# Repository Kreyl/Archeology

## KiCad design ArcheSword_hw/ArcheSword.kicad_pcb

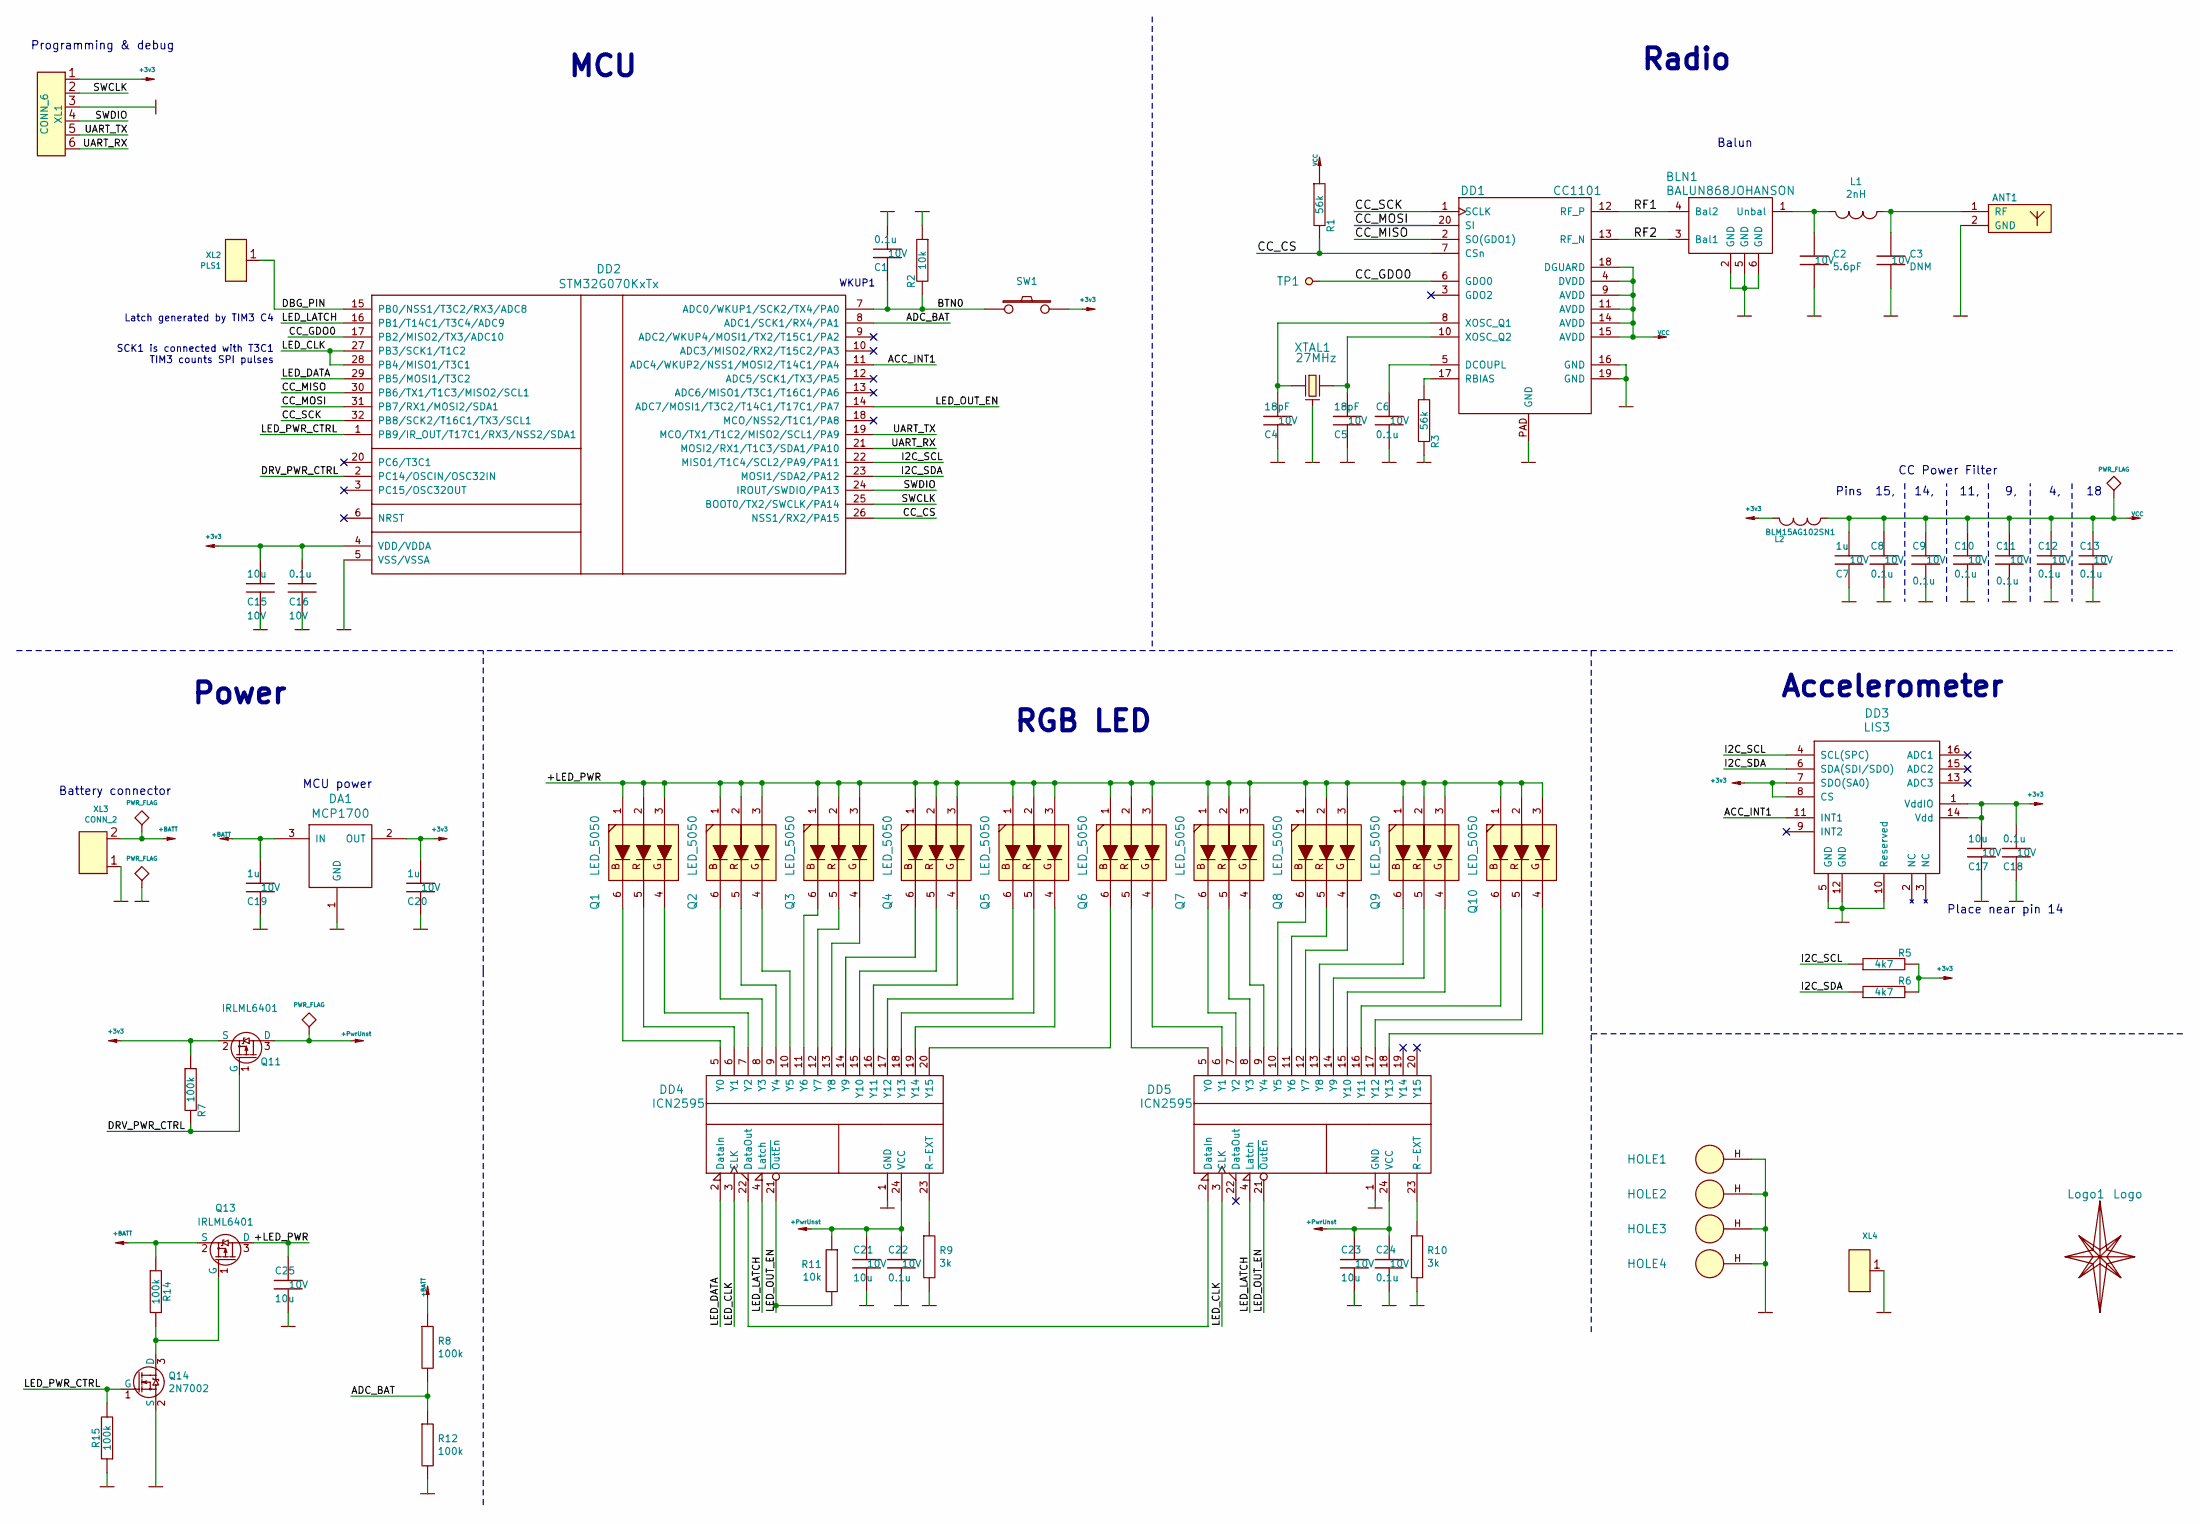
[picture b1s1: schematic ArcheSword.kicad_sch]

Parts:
ANT1: ANT_GENERAL; Locket5
BLN1: BALUN868JOHANSON; BALUN_JOHANSON868
C1, C6, C8, C9, C10, C11, C12, C13, C18, C22, C24: 0.1u; CAP_0603_Silks; Tolerance 20%; Voltage 10V
C2: 5.6pF; CAP_0402; Tolerance 20%; Voltage 10V
C3: DNM; CAP_0402; Tolerance 20%; Voltage 10V
C4, C5: 18pF; CAP_0603_Silks; Tolerance 20%; Voltage 10V
C7, C19, C20: 1u; CAP_0603_Silks; Tolerance 20%; Voltage 10V
C15: 10u; CAP_0603_Silks; Voltage 10V; Tolerance 20%
C16: 0.1u; CAP_0603_Silks; Voltage 10V; Tolerance 20%
C17, C21, C23, C25: 10u; CAP_0603_Silks; Tolerance 20%; Voltage 10V
DA1: MCP1700; SOT23-3A
DD1: CC1101; QFN20
DD2: STM32G070KxTx; TQFP-32_7x7_Pitch0.8mm
DD3: LIS3; LGA16_3X3_5_3
DD4, DD5: ICN2595; TSSOP24_150_0635
HOLE1, HOLE2, HOLE3, HOLE4: HOLE_METALLED; Hole3_5_out6mm
L1: 2nH; IND_0402; Tolerance 20%
L2: BLM15AG102SN1; IND_0402; Tolerance 20%
Logo1: Logo; Ostranna_16d9_13d5
Q1, Q2, Q3, Q4, Q5, Q6, Q7, Q8, Q9, Q10: LED_5050
Q11, Q13: IRLML6401; SOT23-3
Q14: 2N7002; SOT23-3
R1, R3: 56k; RES_0603; Tolerance 1%
R2, R11: 10k; RES_0603; Tolerance 1%
R5, R6: 4k7; RES_0603; Tolerance 1%
R7, R8, R12: 100k; RES_0603; Tolerance 1%
R9, R10: 3k; RES_0603; Tolerance 1%
R14, R15: 100k; RES_0603
SW1: BUTTON; BTN_4x4_SMD
TP1: TESTPOINT; TESTPOINT_1MM
XL1: CONN_6; PLS-6_LOCK
XL2: PLS1; PLS-1Rnd
XL3: CONN_2; SLD_2_2D5
XL4: CONN_1; PLS-1Square
XTAL1: 27MHz; 03225C4

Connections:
+3v3: C15.1, C16.1, C17.1, C18.1, C20.1, DA1.2 (OUT), DD2.4 (VDD/VDDA), DD3.1 (VddIO), DD3.7 (SDO(SA0)), DD3.8 (CS), DD3.14 (Vdd), L2.2, Q11.2 (S), R5.2, R6.2, R7.1, SW1.2, XL1.1
+BATT: C19.1, DA1.3 (IN), Q13.2 (S), R8.1, R14.1, XL3.2 (PM)
+PwrUnst: C21.2, C22.2, C23.2, C24.2, DD4.24 (VCC), DD5.24 (VCC), Q11.3 (D), R11.1
/+LED_PWR: C25.2, Q1.1, Q1.2, Q1.3, Q2.1, Q2.2, Q2.3, Q3.1, Q3.2, Q3.3, Q4.1, Q4.2, Q4.3, Q5.1, Q5.2, Q5.3, Q6.1, Q6.2, Q6.3, Q7.1, Q7.2, Q7.3, Q8.1, Q8.2, Q8.3, Q9.1, Q9.2, Q9.3, Q10.1, Q10.2, Q10.3, Q13.3 (D)
/ACC_INT1: DD2.11 (ADC4/WKUP2/NSS1/MOSI2/T14C1/PA4), DD3.11 (INT1)
/ADC_BAT: DD2.8 (ADC1/SCK1/RX4/PA1), R8.2, R12.1
/BTN0: C1.2, DD2.7 (ADC0/WKUP1/SCK2/TX4/PA0), R2.2, SW1.1
/CC_CS: DD1.7 (CSn), DD2.26 (NSS1/RX2/PA15), R1.2
/CC_GDO0: DD1.6 (GDO0), DD2.17 (PB2/MISO2/TX3/ADC10), TP1.1
/CC_MISO: DD1.2 (SO(GDO1)), DD2.30 (PB6/TX1/T1C3/MISO2/SCL1)
/CC_MOSI: DD1.20 (SI), DD2.31 (PB7/RX1/MOSI2/SDA1)
/CC_SCK: DD1.1 (SCLK), DD2.32 (PB8/SCK2/T16C1/TX3/SCL1)
/DBG_PIN: DD2.15 (PB0/NSS1/T3C2/RX3/ADC8), XL2.1
/DRV_PWR_CTRL: DD2.2 (PC14/OSCIN/OSC32IN), Q11.1 (G), R7.2
/I2C_SCL: DD2.22 (MISO1/T1C4/SCL2/PA9/PA11), DD3.4 (SCL(SPC)), R5.1
/I2C_SDA: DD2.23 (MOSI1/SDA2/PA12), DD3.6 (SDA(SDI/SDO)), R6.1
/LED_CLK: DD2.27 (PB3/SCK1/T1C2), DD2.28 (PB4/MISO1/T3C1), DD4.3 (CLK), DD5.3 (CLK)
/LED_DATA: DD2.29 (PB5/MOSI1/T3C2), DD4.2 (DataIn)
/LED_LATCH: DD2.16 (PB1/T14C1/T3C4/ADC9), DD4.4 (Latch), DD5.4 (Latch)
/LED_OUT_EN: DD2.14 (ADC7/MOSI1/T3C2/T14C1/T17C1/PA7), DD4.21 (~OutEn), DD5.21 (~OutEn), R11.2
/LED_PWR_CTRL: DD2.1 (PB9/IR_OUT/T17C1/RX3/NSS2/SDA1), Q14.1 (G), R15.2
/RF1: BLN1.4 (Bal2), DD1.12 (RF_P)
/RF2: BLN1.3 (Bal1), DD1.13 (RF_N)
/SWCLK: DD2.25 (BOOT0/TX2/SWCLK/PA14), XL1.2
/SWDIO: DD2.24 (IROUT/SWDIO/PA13), XL1.4
/UART_RX: DD2.21 (MOSI2/RX1/T1C3/SDA1/PA10), XL1.6
/UART_TX: DD2.19 (MCO/TX1/T1C2/MISO2/SCL1/PA9), XL1.5
GND: ANT1.2 (GND), BLN1.2 (GND), BLN1.5 (GND), BLN1.6 (GND), C1.1, C2.2, C3.2, C4.2, C5.2, C6.1, C7.2, C8.2, C9.2, C10.2, C11.2, C12.2, C13.2, C15.2, C16.2, C17.2, C18.2, C19.2, C20.2, C21.1, C22.1, C23.1, C24.1, C25.1, DA1.1 (GND), DD1.16 (GND), DD1.19 (GND), DD1.PAD (GND), DD2.5 (VSS/VSSA), DD3.5 (GND), DD3.10 (Reserved), DD3.12 (GND), DD4.1 (GND), DD5.1 (GND), HOLE1.H, HOLE2.H, HOLE3.H, HOLE4.H, Q14.2 (S), R2.1, R3.2, R9.2, R10.2, R12.2, R15.1, XL1.3, XL3.1, XL4.1, XTAL1.H
unnamed: ANT1.1 (RF), C3.1, L1.2
unnamed: BLN1.1 (Unbal), C2.1, L1.1
unnamed: C4.1, DD1.8 (XOSC_Q1), XTAL1.1
unnamed: C5.1, DD1.10 (XOSC_Q2), XTAL1.2
unnamed: C6.2, DD1.5 (DCOUPL)
unnamed: DD1.17 (RBIAS), R3.1
unnamed: DD4.5 (Y0), Q1.6
unnamed: DD4.6 (Y1), Q1.5 (G)
unnamed: DD4.7 (Y2), Q1.4 (B)
unnamed: DD4.8 (Y3), Q2.6
unnamed: DD4.9 (Y4), Q2.5 (G)
unnamed: DD4.10 (Y5), Q2.4 (B)
unnamed: DD4.11 (Y6), Q3.6
unnamed: DD4.12 (Y7), Q3.5 (G)
unnamed: DD4.13 (Y8), Q3.4 (B)
unnamed: DD4.14 (Y9), Q4.6
unnamed: DD4.15 (Y10), Q4.5 (G)
unnamed: DD4.16 (Y11), Q4.4 (B)
unnamed: DD4.17 (Y12), Q5.6
unnamed: DD4.18 (Y13), Q5.5 (G)
unnamed: DD4.19 (Y14), Q5.4 (B)
unnamed: DD4.20 (Y15), Q6.6
unnamed: DD4.22 (DataOut), DD5.2 (DataIn)
unnamed: DD4.23 (R-EXT), R9.1
unnamed: DD5.5 (Y0), Q6.5 (G)
unnamed: DD5.6 (Y1), Q6.4 (B)
unnamed: DD5.7 (Y2), Q7.6
unnamed: DD5.8 (Y3), Q7.5 (G)
unnamed: DD5.9 (Y4), Q7.4 (B)
unnamed: DD5.10 (Y5), Q8.6
unnamed: DD5.11 (Y6), Q8.5 (G)
unnamed: DD5.12 (Y7), Q8.4 (B)
unnamed: DD5.13 (Y8), Q9.6
unnamed: DD5.14 (Y9), Q9.5 (G)
unnamed: DD5.15 (Y10), Q9.4 (B)
unnamed: DD5.16 (Y11), Q10.6
unnamed: DD5.17 (Y12), Q10.5 (G)
unnamed: DD5.18 (Y13), Q10.4 (B)
unnamed: DD5.23 (R-EXT), R10.1
unnamed: Q13.1 (G), Q14.3 (D), R14.2
VCC: C7.1, C8.1, C9.1, C10.1, C11.1, C12.1, C13.1, DD1.4 (DVDD), DD1.9 (AVDD), DD1.11 (AVDD), DD1.14 (AVDD), DD1.15 (AVDD), DD1.18 (DGUARD), L2.1, R1.1

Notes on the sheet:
Programming & debug
Battery connector
Power
Latch generated by TIM3 C4
SCK1 is connected with T3C1 TIM3 counts SPI pulses
MCU power
MCU
WKUP1
RGB LED
Radio
Balun
Accelerometer
Pins 15, 14, 11, 9, 4, 18
CC Power Filter
Place near pin 14

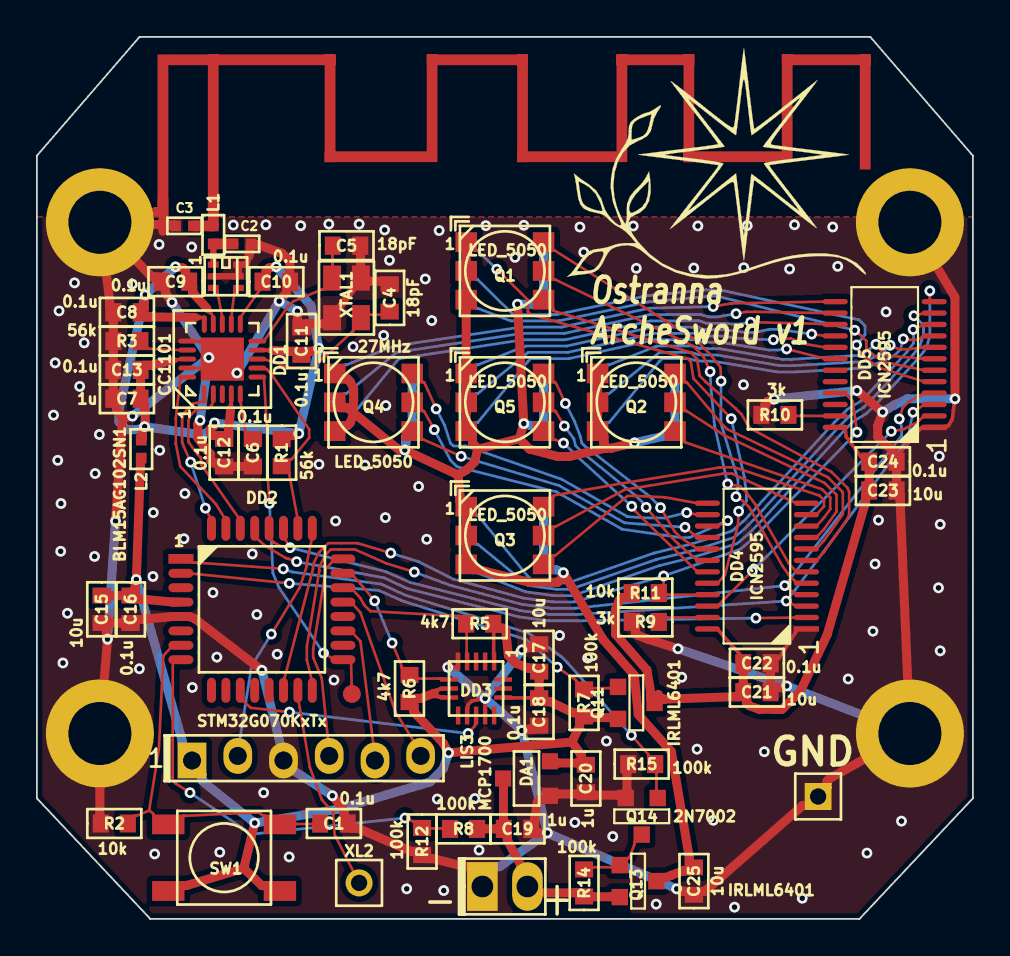
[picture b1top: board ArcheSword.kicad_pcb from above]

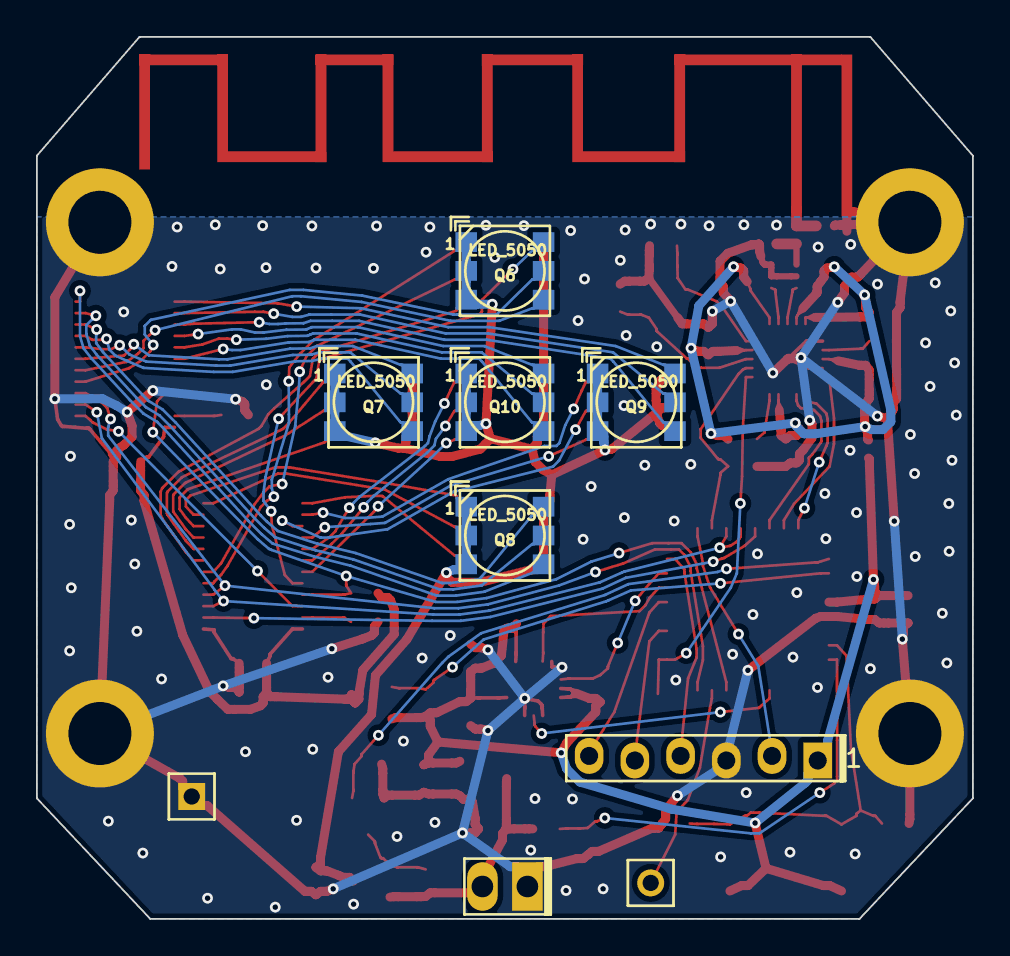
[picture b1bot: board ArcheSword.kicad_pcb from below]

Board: 2 copper layers, 52.0 x 49.0 mm, 72 parts (5 on the bottom side), 69 nets.

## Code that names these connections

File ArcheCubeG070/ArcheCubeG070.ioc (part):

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Mcu.Name=STM32G070KBTx
Mcu.Package=LQFP32
Mcu.UserName=STM32G070KBTx
PA0.Mode=SYS_WakeUp0
PA0.Signal=SYS_WKUP1
PA1.Mode=IN1
PA1.Signal=ADC1_IN1
PA10.Mode=Asynchronous
PA10.Signal=USART1_RX
PA11\ [PA9].Mode=I2C
PA11\ [PA9].Signal=I2C2_SCL
PA12\ [PA10].Mode=I2C
PA12\ [PA10].Signal=I2C2_SDA
PA13.Mode=Serial_Wire
PA13.Signal=SYS_SWDIO
PA14-BOOT0.Mode=Serial_Wire
PA14-BOOT0.Signal=SYS_SWCLK
PA15.Signal=GPIO_Output
PA2.Signal=GPIO_Output
PA4.Mode=SYS_WakeUp1
PA4.Signal=SYS_WKUP2
PA7.Signal=S_TIM3_CH2
PA9.Mode=Asynchronous
PA9.Signal=USART1_TX
PB0.Signal=GPIO_Output
PB1.Signal=S_TIM3_CH4
PB2.Signal=GPIO_Input
PB3.Mode=TX_Only_Simplex_Unidirect_Master
PB3.Signal=SPI1_SCK
PB4.Signal=S_TIM3_CH1
PB5.Mode=TX_Only_Simplex_Unidirect_Master
PB5.Signal=SPI1_MOSI
PB6.Mode=Full_Duplex_Master
PB6.Signal=SPI2_MISO
PB7.Mode=Full_Duplex_Master
PB7.Signal=SPI2_MOSI
PB8.Mode=Full_Duplex_Master
PB8.Signal=SPI2_SCK
PB9.Signal=GPIO_Output
PC14-OSC32_IN\ (PC14).Signal=GPIO_Output
RCC.HSE_VALUE=8000000
RCC.SYSCLKFreq_VALUE=64000000
RCC.SYSCLKSource=RCC_SYSCLKSOURCE_PLLCLK
board=custom

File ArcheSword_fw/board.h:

#pragma once

// ==== General ====
#define BOARD_NAME          "ArcheoSword"
#define APP_NAME            "ArcheoSword"

#define LSE_FREQ_HZ     32768   // Left it here even if not used

// ST driver system settings
#define STM32_ST_IRQ_PRIORITY   2
#define STM32_ST_USE_TIMER      15

#ifndef TRUE
#define TRUE            1
#endif

#if 1 // ========================== GPIO =======================================
// UART
#define UART_GPIO       GPIOA
#define UART_TX_PIN     9
#define UART_RX_PIN     10

// I2C
#define SCL2_GPIO       GPIOA
#define SCL2_PIN        11
#define SDA2_GPIO       GPIOA
#define SDA2_PIN        12
#define I2C2_AF         AF6

// Counts
#define LED_CNT         10UL // Max
#define LED_CHNL_CNT    (LED_CNT * 3UL)
#define LED_BYTE_CNT    4UL // 2 ICs, 32 bits
#define LED_WORD_CNT    2UL // DISP_BYTE_CNT / 2
#define LED_IC_CNT      2UL

// Debug pin
#define DBG_PIN         GPIOB, 0
#define DBG_HI()        PinSetHi(DBG_PIN)
#define DBG_LO()        PinSetLo(DBG_PIN)
#define DBG_TOGGLE()    PinToggle(DBG_PIN)

// LEDs
#define TIMESLOT_TOP    255UL
#define OUT_EN_PIN      GPIOA, 7, omPushPull, pudNone, AF1
#define LATCH_TMR       TIM3
#define LEDS_SPI        SPI1
#define LATCH_TMR_IN    GPIOB, 4, omPushPull, pudPullDown, AF1
#define LATCH_PIN       GPIOB, 1, omPushPull, pudNone, AF1
#define LED_DATA        GPIOB, 5, omPushPull, pudNone, AF0
#define LED_CLK         GPIOB, 3, omPushPull, pudNone, AF0
#define LED_PWR_CTRL    GPIOB, 9
#define DRV_PWR_CTRL    GPIOC, 14

// Radio: SPI, PGpio, Sck, Miso, Mosi, Cs, Gdo0
#define CC_Setup0       SPI2, GPIOB, 8,6,7, GPIOA,15, GPIOB,2

// Acc
#define ACG_IRQ_PIN     GPIOA, 4

#define ADC_BAT         GPIOA, 1

// Button
#define BTN_PIN         GPIOA, 0
#endif // GPIO

#if 1 // =========================== I2C =======================================
#define I2C1_ENABLED        FALSE
#define I2C2_ENABLED        FALSE
#define I2C_BAUDRATE_HZ     400000
#define I2C_USE_DMA         FALSE
#endif

#if 1 // =========================== ADC =======================================
#define ADC_ENABLED     FALSE
#define ADC_CHNL_CNT    2 // Tsns and VRef

#endif

#if 1 // =========================== Timers ====================================
#define LEDS_TIM        TIM3
#define LEDS_TIM_IRQ_VECTOR TIM3_IRQHandler

#define TIME_TIMER      TIM7
#define ADC_TIMER       TIM6

#endif


#if 1 // =========================== DMA =======================================
// ==== Uart ====
#define UART_DMA_TX_CHNL    7
#define UART_DMA_TX_REQID   51 // p223 of refman
#define UART_DMA_RX_CHNL    6
#define UART_DMA_RX_REQID   50 // p223 of refman

#define UART_DMA_TX_MODE (  DMA_PRIORITY_LOW | \
                            DMA_MSIZE_8_BIT | \
                            DMA_PSIZE_8_BIT | \
                            DMA_MEM_INC |       /* Memory pointer increase */ \
                            DMA_DIR_MEM2PER |    /* Direction is memory to peripheral */ \
                            DMA_TCIE         /* Enable Transmission Complete IRQ */)

#define UART_DMA_RX_MODE (  DMA_PRIORITY_MEDIUM | \
                            DMA_MSIZE_8_BIT | \
                            DMA_PSIZE_8_BIT | \
                            DMA_MEM_INC |       /* Memory pointer increase */ \
                            DMA_DIR_PER2MEM |    /* Direction is peripheral to memory */ \
                            DMA_CIRC         /* Circular buffer enable */)

// ==== LEDs ====
#define LEDS_DMA_TX_CHNL    1
#define LEDS_DMA_TX_REQID   17 // SPI1 TX, p223 of refman


// ==== I2C1 ====
#define I2C1_DMA_TX_CHNL    5
#define I2C1_DMA_TX_REQID   11
#define I2C1_DMA_RX_CHNL    4
#define I2C1_DMA_RX_REQID   10

// ==== ADC ====
//#define ADC_DMA_CHNL
//#define ADC_DMA_REQID       5

#endif // DMA

#if 1 // ========================== USART ======================================
#define PRINTF_FLOAT_EN     FALSE
#define UART_TXBUF_SZ       512
#define UART_RXBUF_SZ       256
#define CMD_BUF_SZ          128
#define UART_CHAR_TO_IRQ    '\n'

#define CMD_UART_PARAMS \
    USART1, UART_GPIO, UART_TX_PIN, UART_GPIO, UART_RX_PIN, \
    UART_DMA_TX_CHNL, UART_DMA_RX_CHNL, \
    UART_DMA_TX_MODE, UART_DMA_RX_MODE,\
    UART_DMA_TX_REQID, UART_DMA_RX_REQID, \
    uartclkPCLK

#endif

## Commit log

2021-08-04 PCB produced, code started
2021-08-07 + Radio works
2021-08-07 + Leds work ok + Leds as RGB sequencer
2021-08-08 * Logic changed: timeout resets always, new color shows when chnl/color has changed. RC
